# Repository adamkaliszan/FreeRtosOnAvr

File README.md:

# FreeRtosOnAvr

An alternative for arduino. Multitasking firmware provides great flexibility.

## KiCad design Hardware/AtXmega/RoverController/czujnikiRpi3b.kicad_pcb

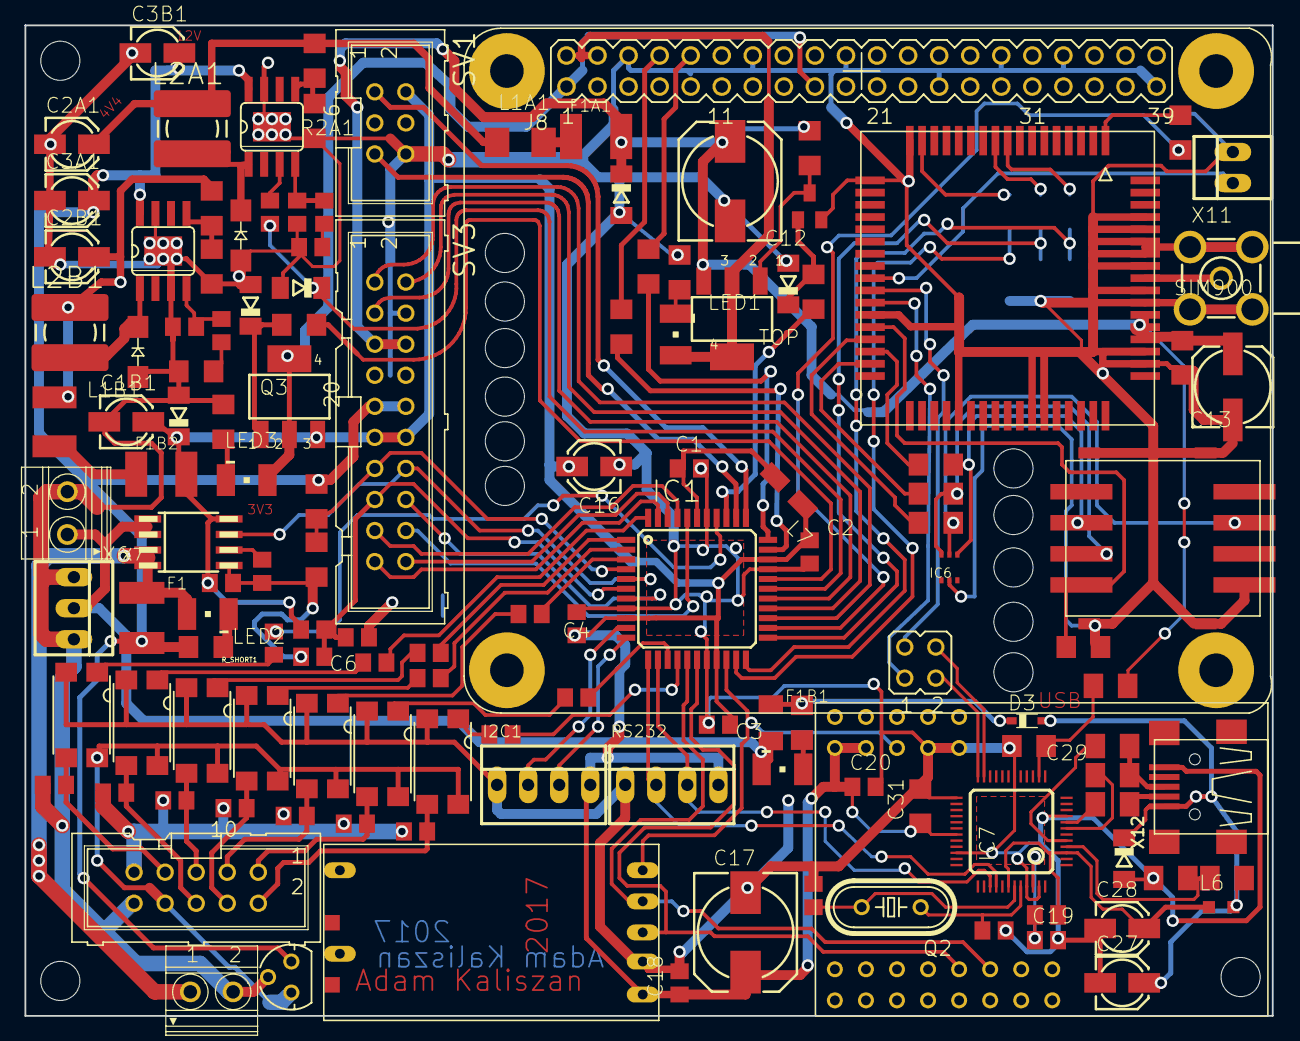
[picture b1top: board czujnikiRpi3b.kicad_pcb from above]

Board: 2 copper layers, 102.0 x 81.0 mm, 157 parts (0 on the bottom side), 110 nets.

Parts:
@HOLE0, @HOLE1, @HOLE2, @HOLE3, @HOLE4, @HOLE5, @HOLE6, @HOLE7, @HOLE8, @HOLE9, @HOLE10, @HOLE11, @HOLE12, @HOLE13: (no value)
C1, C2, C3, C4, C6, C18, C19, C20: C-EUC0805; C0805
C1B1, C2A1, C2B1, C3A1, C3B1, C16, C27, C28: CPOL-EU153CLV-0405; 153CLV-0405
C4A1, C4B1: 22nF; C0805
C5, C21: 100nF; C1206
C5A1, C5B1: 220pF; C0805
C12, C17: CPOL-EU140CLH-0810; 140CLH-0810
C13: CPOL-EU153CLV-0605; 153CLV-0605
C29, C31: C-EUC1206; C1206
C33, C34: 12pf; C0805
CI1: 100nF; C0805
CI2: 1nF; C0805
D1A1, D1B1: B350A-13-F; SMA-DO214AC
D3: BAT60J; SOD323_ST
F1, F1A1, F1B2: PICOFUSE1812; C1812K
F1B1: PICOFUSE1206; C1206K
I2C1: 22-23-2041
IC1: XMEGA16A4A; TQFP44
IC2: SIM900
IC3, IC4: L5973D; HSOP8-PAD
IC5: 78LXX
IC6: SMF05C; SC-70-6
IC7: FT2232C; LQFP
JP_CPU1: JP2Q
L1A1: 47@1000; L4532M
L1B1: 47@1000; L4532P
L2A1, L2B1: 15µH; POWER-CHOKE_WE-TPC
L6: L-EUL2012C; L2012C
L7: L-EUL4035M; L4035M
LED1, LED2, LED3: _T679-?-1D2E2; PLCC2
LED_USB_FAULT1: _T679-?-1D2E2; PLCC2
OK_A1, OK_A2: LTV816S; SMD4
OK_B1, OK_B2: LTV816S; SMD4
OK_HEN1: LTV816S; SMD4
OK_PWMA1: LTV816S; SMD4
OK_PWMB1: LTV816S; SMD4
PCB1: RASPBERRY_PI_B+TPLACE_A; RASPBERRY_PI_APLUS_TPLACE
P_PDIV2: 2k2; R1206
Q1: BC817; SOT23-BEC
Q2: CRYSTALHC49S; HC49_S
Q3, Q4: BSP170P; SOT223
R1, R2: 27; M1206
R1A1: 8k2; R1206
R1B1: 5k6; R1206
R1RPI1, R2RPI1: 56k; R1206
R2A1, R2B1: 3k3; R1206
R3: 1k5; M1206
R3A1: 4k7; R0805
R3B1: 4k7; R1206
R3RPI1, R3RPI2, R3RPI3, R3RPI4: 1k; R1206
R4: 470; M0805
R4A1: 3k3; R0805
R5: 4k7; M1206
R6: 10k; M1206
R7: 0; M1206
RS232: 22-23-2041
R_A1IN1, R_A1IN2, R_A2IN1, R_A2IN2: 1k; R0805
R_B1IN1, R_B1IN2, R_B2IN1, R_B2IN2: 1k; R0805
R_HEN1, R_HEN2: 1k; R0805
R_PDIV1: 56k; R1206
R_PWMA1, R_PWMA2: 1k; R0805
R_PWMB1, R_PWMB2: 1k; R0805
R_PWR1: 56k; R0805
R_PWR2: 12k; R0805
R_RPI2: 56k; R1206
R_SHORT1: 1k; R1206
R_SHORT_USB1: 1k; R1206
R_SIM1, R_SIM2, R_SIM3: 22; R1206
R_SIM4, R_SIM5, R_SIM6, R_SIM7: 1k; R1206
SV1: ML6
SV2: ML10E; ML10
SV3: ML20E; ML20
U$3: HC-12
U$4: XCORE2530
U$5, U$6: LOGO
U$7: SCU-W0822XR-06115R-BCA0; 115R-BCA0
U$8: ACS712SO8; SO-08M
X2, X6: 1751248
X7: 22-23-2031
X9: 22-23-2021
X11: BU-SMA-H
X12: USB-SHIELD; USB-M-S1
ZD1A1: 5v1; SOD80C
ZD1B1, ZD1B2, ZD1B3, ZD1B4, ZD1B5, ZD1B14, ZD1B15, ZD2A1: 3v6; SOD80C
ZD_USB1: 5v6; SOD80C

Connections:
+3V3: C1B1.+, C2.1, C3.1, C4.1, C5.1, C12.+, C13.+, C16.+, C17.+, C18.1, C20.1, C31.1, CI1.1, F1A1.2, F1B2.2, I2C1.4, IC1.9, IC1.19, IC1.31, IC2.55, IC2.56, IC2.57, IC7.31, L7.1, Q3.3, Q4.3, R2RPI1.2, R7.2, RS232.4, R_PWR1.2, SV1.2, SV3.5, SV3.6, SV3.11, SV3.12, U$3.P$1, U$4.P$1B, U$4.P$3B, U$8.8, ZD1A1.C, ZD1B1.C
+12V: C3A1.+, C3B1.+, F1.2, IC3.8, IC4.8, IC5.IN, R_PDIV1.2, R_SHORT1.2, SV3.9, SV3.10
/czujnikiRpi3b_1/A1_IN: OK_A1.1, R_A1IN1.1
/czujnikiRpi3b_1/A2_IN: OK_A2.1, R_A2IN1.1
/czujnikiRpi3b_1/B1_IN: OK_B2.1, R_B1IN1.2
/czujnikiRpi3b_1/B2_IN: OK_B1.1, R_B2IN1.2
/czujnikiRpi3b_1/PA0: IC1.40, SV3.18
/czujnikiRpi3b_1/PA1: IC1.41, SV3.17
/czujnikiRpi3b_1/PA2: IC1.42, SV3.20
/czujnikiRpi3b_1/PA3: IC1.43, SV3.19
/czujnikiRpi3b_1/PA4: IC1.44, R_B1IN1.1
/czujnikiRpi3b_1/PA5: IC1.1, R_A2IN1.2
/czujnikiRpi3b_1/PA6: IC1.2, R_B2IN1.1
/czujnikiRpi3b_1/PA7: IC1.3, R_A1IN1.2
/czujnikiRpi3b_1/PB0: IC1.4, P_PDIV2.2, R_PDIV1.1, SV3.13
/czujnikiRpi3b_1/PB1: IC1.5, SV3.14, U$8.7
/czujnikiRpi3b_1/PB2: C6.1, IC1.6, R_PWR1.1, R_PWR2.2, SV3.15
/czujnikiRpi3b_1/PB3: IC1.7, SV3.16
/czujnikiRpi3b_1/PC4: IC1.14, R_PWMA1.1
/czujnikiRpi3b_1/PC5: IC1.15, R_PWMB1.2
/czujnikiRpi3b_1/PC6: IC1.16, U$3.P$4
/czujnikiRpi3b_1/PC7: IC1.17, U$3.P$3
/czujnikiRpi3b_1/PD0: IC1.20, U$3.P$5, U$4.P$5B
/czujnikiRpi3b_1/PD1: IC1.21, R_SIM7.2, ZD1B2.C
/czujnikiRpi3b_1/PD2: IC1.22, R_SIM5.2, ZD1B4.C
/czujnikiRpi3b_1/PD3: IC1.23, R_SIM6.2, ZD1B3.C
/czujnikiRpi3b_1/PD4: IC1.24, R_SIM4.2, ZD1B5.C
/czujnikiRpi3b_1/PD5: IC1.25, SV3.1
/czujnikiRpi3b_1/PD6: IC1.26, SV3.2
/czujnikiRpi3b_1/PD7: IC1.27, SV3.3
/czujnikiRpi3b_1/PR1: IC1.37, R_HEN1.2
/czujnikiRpi3b_1/PWMA: OK_PWMA1.1, R_PWMB1.1
/czujnikiRpi3b_1/PWMB: OK_PWMB1.1, R_PWMA1.2
DBG_RX: IC2.28, JP_CPU1.1
DBG_TX: IC2.27, JP_CPU1.3
EXT_RX: IC1.12, IC7.40, RS232.2
EXT_TX: IC1.13, IC7.39, RS232.3
GND: C1.2, C1B1.-, C2.2, C2A1.-, C2B1.-, C3.2, C3A1.-, C3B1.-, C4.2, C5.2, C5A1.2, C5B1.2, C6.2, C12.-, C13.-, C16.-, C17.-, C18.2, C19.2, C20.2, C21.2, C27.-, C28.-, C29.2, C31.2, C33.2, C34.2, CI1.2, CI2.2, D1A1.A, D1B1.A, I2C1.1, IC1.8, IC1.18, IC1.30, IC1.38, IC2.17, IC2.18, IC2.29, IC2.39, IC2.45, IC2.46, IC2.53, IC2.54, IC2.58, IC2.59, IC2.61, IC2.62, IC2.63, IC2.64, IC2.65, IC3.7, IC3.P, IC4.3, IC4.7, IC4.P, IC5.GND, IC6.2, IC7.9, IC7.18, IC7.25, IC7.34, IC7.45, IC7.47, OK_A1.2, OK_A2.2, OK_B1.2, OK_B2.2, OK_HEN1.2, OK_PWMA1.2, OK_PWMB1.2, PCB1.6, PCB1.9, PCB1.14, PCB1.20, PCB1.25, PCB1.30, PCB1.34, PCB1.39, P_PDIV2.1, Q1.E, R2A1.1, R2B1.1, R3A1.1, R3B1.1, R3RPI1.1, R3RPI4.1, R6.1, RS232.1, R_A1IN2.1, R_A2IN2.1, R_B1IN2.2, R_B2IN2.1, R_HEN2.2, R_PWMA2.2, R_PWMB2.1, R_PWR2.1, SV1.6, SV2.9, SV2.10, SV3.4, SV3.7, SV3.8, U$3.P$2, U$4.P$7B, U$4.P$9B, U$7.C5, U$7.P$1, U$7.P$2, U$7.P$3, U$7.P$4, U$8.5, X2.2, X6.2, X7.1, X7.3, X9.2, X11.2, X11.3, X11.4, X11.5, X12.GND, ZD1A1.A, ZD1B1.A, ZD1B2.A, ZD1B3.A, ZD1B4.A, ZD1B5.A, ZD1B14.A, ZD1B15.A, ZD2A1.A, ZD_USB1.A
unnamed: C1.1, IC1.39, L7.2
unnamed: C2A1.+, L1A1.1, L2A1.1, R1A1.2
unnamed: C2B1.+, L1B1.1, L2B1.1, R1B1.2
unnamed: C4A1.1, C5A1.1, IC3.4
unnamed: C4A1.2, R3A1.2
unnamed: C4B1.1, C5B1.1, IC4.4
unnamed: C4B1.2, R3B1.2
unnamed: C19.1, IC7.46, R4.1
unnamed: C21.1, IC2.30, U$7.C1
unnamed: C28.+, IC7.3, IC7.42, L6.1, R4.2
unnamed: C29.1, IC7.14, R7.1
unnamed: C33.1, IC7.43, Q2.2
unnamed: C34.1, IC7.44, Q2.1
unnamed: CI2.1, U$8.6
unnamed: D1A1.K, IC3.1, L2A1.2
unnamed: D1B1.K, IC4.1, L2B1.2
unnamed: F1.1, LED2.A, U$8.3, U$8.4, X2.1
unnamed: F1A1.1, L1A1.2
unnamed: F1B1.2, LED_USB_FAULT1.C, U$8.1, U$8.2, X6.1, X7.2
unnamed: F1B2.1, L1B1.2
unnamed: IC1.28, R4A1.2, ZD2A1.C
unnamed: IC1.29, R_RPI2.1
unnamed: IC1.32, R3RPI2.1
unnamed: IC1.33, R3RPI3.1
unnamed: IC1.34, SV1.1
unnamed: IC1.35, SV1.5
unnamed: IC1.36, R1RPI1.2
unnamed: IC2.1, R_SIM4.1
unnamed: IC2.9, R_SIM5.1
unnamed: IC2.10, R_SIM6.1
unnamed: IC2.16, R_SIM7.1
unnamed: IC2.26, X9.1
unnamed: IC2.31, R_SIM1.2
unnamed: IC2.32, R_SIM3.1
unnamed: IC2.33, R_SIM2.2
unnamed: IC2.60, X11.1
unnamed: IC3.3, R4A1.1
unnamed: IC3.5, R1A1.1, R2A1.2
unnamed: IC4.5, R1B1.1, R2B1.2
unnamed: IC5.OUT, OK_A1.4, OK_A2.4, OK_B1.4, OK_B2.4, OK_HEN1.4, OK_PWMA1.4, OK_PWMB1.4, SV2.8
unnamed: IC6.4, R_SIM3.2, U$7.C3
unnamed: IC6.5, R_SIM1.1, U$7.C7
unnamed: IC6.6, R_SIM2.1, U$7.C2
unnamed: IC7.4, R5.1, R6.2
unnamed: IC7.5, R3.2
unnamed: IC7.7, R2.2
unnamed: IC7.8, R1.2
unnamed: IC7.23, JP_CPU1.4
unnamed: IC7.24, JP_CPU1.2
unnamed: LED1.A, PCB1.2, PCB1.4, Q4.2, Q4.4
unnamed: LED1.C, R3RPI4.2
unnamed: LED2.C, R_SHORT1.1
unnamed: LED3.A, PCB1.1, PCB1.17, Q3.2, Q3.4
unnamed: LED3.C, R3RPI1.2
unnamed: LED_USB_FAULT1.A, R_SHORT_USB1.1
unnamed: OK_A1.3, R_A1IN2.2, SV2.3
unnamed: OK_A2.3, R_A2IN2.2, SV2.5
unnamed: OK_B1.3, R_B1IN2.1, SV2.4
unnamed: OK_B2.3, R_B2IN2.2, SV2.6
unnamed: OK_HEN1.1, R_HEN1.1
unnamed: OK_HEN1.3, R_HEN2.1, SV2.7
unnamed: OK_PWMA1.3, R_PWMB2.2, SV2.2
unnamed: OK_PWMB1.3, R_PWMA2.1, SV2.1
unnamed: PCB1.8, R3RPI2.2
unnamed: PCB1.10, R3RPI3.2
unnamed: Q1.B, R1RPI1.1, ZD1B14.C
unnamed: Q1.C, Q4.1, R2RPI1.1
unnamed: Q3.1, R_RPI2.2, ZD1B15.C
unnamed: R1.1, X12.D-
unnamed: R2.1, R3.1, X12.D+
PWR_USB: D3.C, F1B1.1, R_SHORT_USB1.2
V_USB: C27.+, D3.A, L6.2, R5.2, X12.VBUS, ZD_USB1.C

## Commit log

2018-01-04 Initial version
2018-01-04 Hardware schematics and PCB boards
2018-01-09 New subprojet DVR Controller
2018-01-11 DVR function for output controll
2018-01-18 AVR io helper for codeblocks
2018-01-18 atxmega helper
2018-01-20 ADC support
    Internal and power suply voltage mesarument.
    Current controll si not calibrated
2019-07-13 Migration to MPlab
2019-07-21 FTDI eeprom settings, avrdude upload scripts
2019-07-21 compuler custom: xc8 and avr-gcc
2019-09-17 Rover project
    Rover project has been converted to MPLAB ide
2019-09-17 Obsolete projects
2019-09-18 Rover Project CLI
    First working version of rower project
2019-09-22 Code refactorization
    Common libraries for xc8 and ave-gcc compiler
2019-09-22 I2C
    Initial files
2019-09-27 TWI in progress
2019-09-28 CLI can write and send TWI data
2019-09-29 new CLI
2019-09-29 preparing history
2019-10-02 CLI memory optimization
2019-10-11 CLI history in progress
2019-10-12 History is working. Some bugs in inserting
2019-10-13 CLI edit is working
2019-10-13 New memory optimized approach
2019-10-15 Preparing for ibus support
2019-10-16 RoverController hardware project imported from eagle
2019-10-19 Two variants of CLI history, version with non shared bufffers is working
2019-10-20 Some bug fixes for CLI history shared buffer
2019-10-20 Some bug fixes for CLI history shared buffer 2
2019-10-20 Twi fight
2020-05-03 I2c bugfix
2020-05-03 cleaning up conflicts
2020-05-03 Twi driver in progress
2020-05-09 TWI driver
2020-05-12 CLI optimization
2020-05-19 CLI history is working
2020-05-22 Command copletition by TAB key
2020-05-23 ADXL 345 is working
2020-05-24 Magnetometer support. Bugs wit float numbers stinn not solved
2020-05-26 Gcc cli bug fixes
2020-05-27 Barometer is working
2020-05-29 gyroscope module
2020-05-31 Gyro bug fixes
2020-05-31 twi driver optimization
2020-06-13 Rc ibus
2020-06-13 FreeRTOS core improvements
2020-06-14 Rc controll is working
2023-04-09 Initial cnanges nothing works
2023-04-09 Tixed include nightmre
